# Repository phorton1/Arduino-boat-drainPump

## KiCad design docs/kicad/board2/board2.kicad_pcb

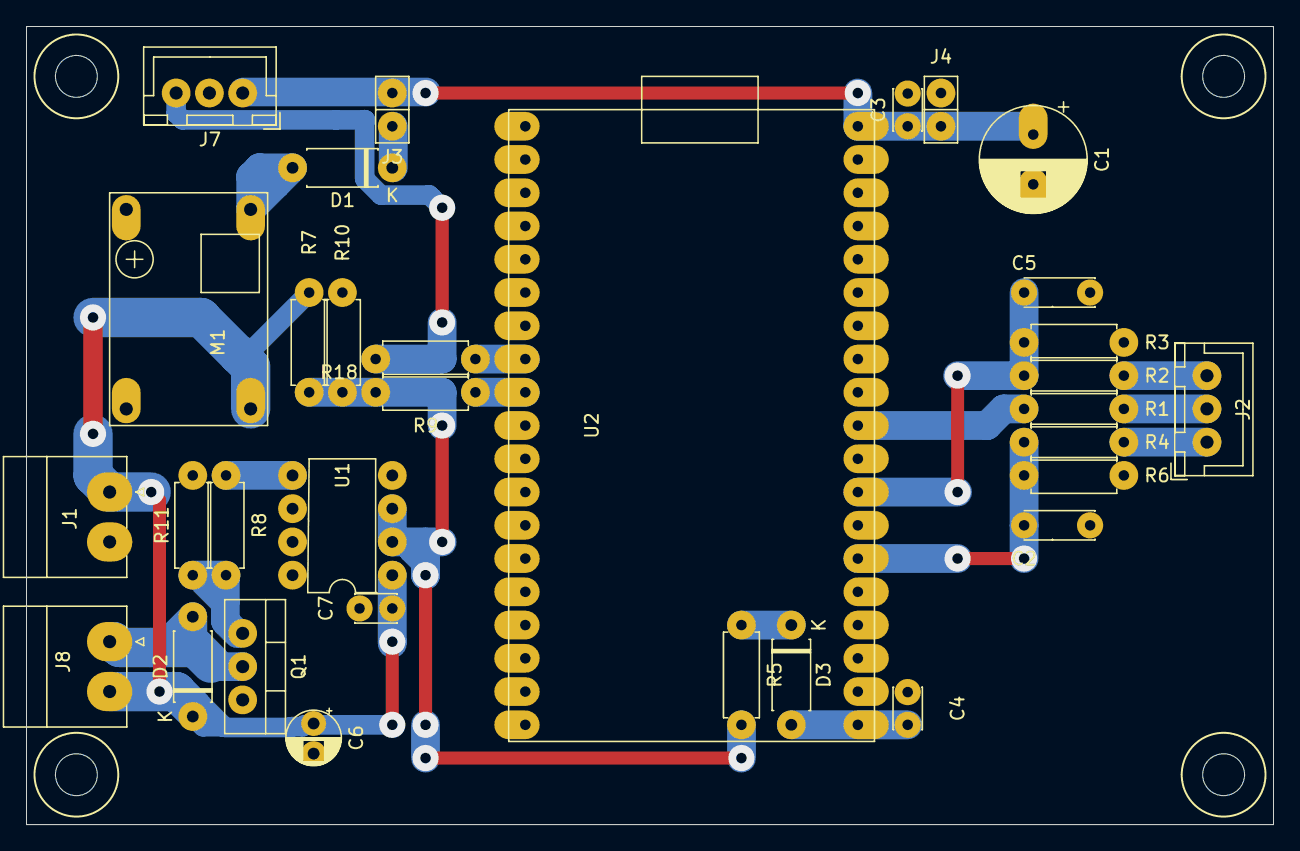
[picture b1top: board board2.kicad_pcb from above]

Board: 2 copper layers, 95.2 x 61.0 mm, 32 parts (0 on the bottom side), 20 nets.

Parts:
C1: 100uf; CP_my100uf
C2, C5: 2.2uf; myCapTantulum2
C3, C4, C7: 0.1uf; myCapCeramicSmall
C6: 10uf; CP_my10uf
D1: 1N4003; myDiodeSchotsky
D2, D3: 1N5818; myDiodeSchotsky
J1: 12 IN; myPheonix2x3.81_right
J2: SENSOR_ASSY; myJSTx03
J3: 5V Jump; myPinHeader_1x02
J4: 5V Test; myPinSocket_1x02
J7: WS2812_B; myJSTx03
J8: PUMP; myPheonix2x3.81_right
M1: BUCK01; buck-mini360
Q1: IRF520N; myThreeLegged
R1, R2, R4: 1K; myResistor
R3, R6, R7: 100K; myResistor
R5, R11: 10K; myResistor
R8: 100; myResistor
R9: 220; myResistor
R10: 33K; myResistor
R18: 330; myResistor
U1: IR2104; myDip8
U2: ESP32_DEV; esp32_dev

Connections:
+3V3: C4.1, D3.2, U2.19
+5V: C1.1, C3.1, J3.2, J4.2, J7.1, U2.1
DRIVE_ROD: J2.2, R1.1
GND: C1.2, C2.2, C3.2, C4.2, C5.2, C6.2, C7.2, J1.2, J4.1, J7.2, M1.1, M1.2, Q1.3, R3.2, R6.2, R10.2, R11.2, U1.4, U2.6, U2.20, U2.26
unnamed: D1.1, J3.1
unnamed: D1.2, M1.3
unnamed: D3.1, R5.1
unnamed: J7.3, R18.2
unnamed: Q1.1, R8.2, R11.1
unnamed: R8.1, U1.5
unnamed: R5.2, R7.2, R9.2, R10.1, U1.2, U1.3
PUMP: R9.1, U2.30
PUMP+: C6.1, C7.1, D2.1, J1.1, J8.2, M1.4, R7.1, U1.1
PUMP-: D2.2, J8.1, Q1.2
ROD_HIGH: J2.3, R2.1
ROD_LOW: J2.1, R4.1
SENSOR_HIGH: C5.1, R2.2, R3.1, U2.12
SENSOR_LOW: C2.1, R4.2, R6.1, U2.14
S_DRIVE: R1.2, U2.10
WS2812B: R18.1, U2.31

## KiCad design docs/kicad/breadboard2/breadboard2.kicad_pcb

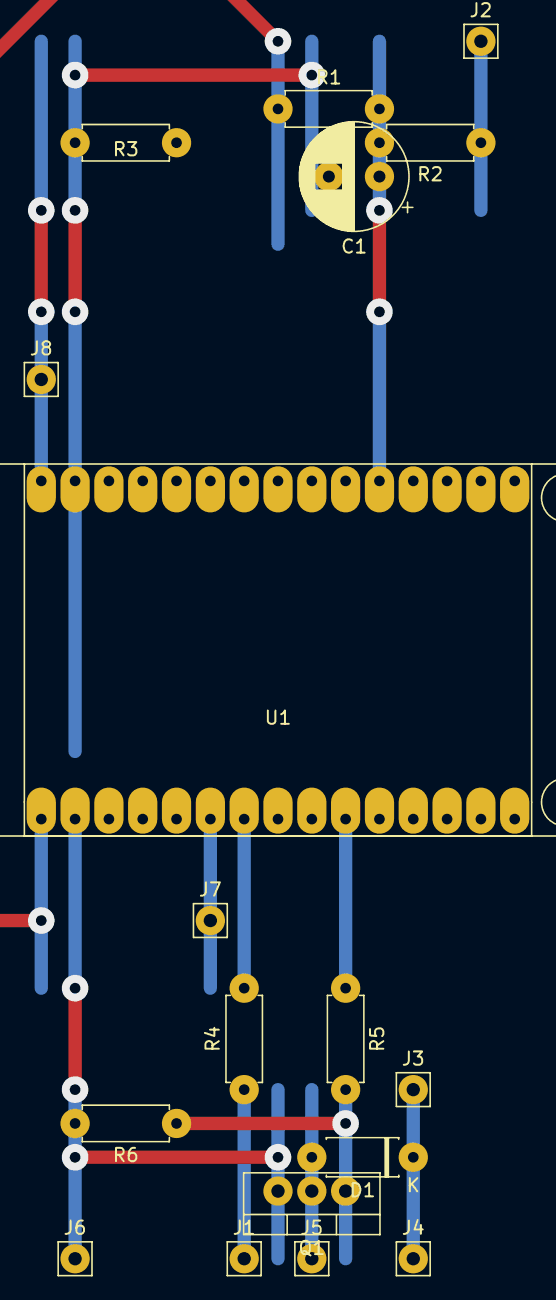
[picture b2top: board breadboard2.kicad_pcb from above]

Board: 2 copper layers, 18 parts (0 on the bottom side), 12 nets.

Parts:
C1: 1uf; CP_my100uf
D1: 1N5818; myDiodeSchotsky
J1: DRIVE_ROD; myPinHeader_1x01
J2: ROD_LOW; myPinHeader_1x01
J3: 12V; myPinHeader_1x01
J4: PUMP+; myPinHeader_1x01
J5: PUMP-; myPinHeader_1x01
J6: GND; myPinHeader_1x01
J7: WS28128B; myPinHeader_1x01
J8: 5V; myPinHeader_1x01
Q1: IRF520N; myThreeLegged
R1: 1M; myResistor
R2, R5: 220; myResistor
R3: 47K; myResistor
R4: 1K; myResistor
R6: 10K; myResistor
U1: ESP32_DEV_0; esp32_dev_0

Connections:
+3V3: R1.1, U1.30
+5V: J8.1, U1.1
DRIVE_ROD: J1.1, R4.1
GND: C1.2, J6.1, Q1.3, R3.2, R6.2, U1.2, U1.29
unnamed: Q1.1, R5.2, R6.1
PUMP: R5.1, U1.21
PUMP+: D1.1, J3.1, J4.1
PUMP-: D1.2, J5.1, Q1.2
ROD_LOW: J2.1, R2.1
SENSOR_LOW: C1.1, R1.2, R2.2, R3.1, U1.11
S_DRIVE: R4.2, U1.24
WS2812B: J7.1, U1.25

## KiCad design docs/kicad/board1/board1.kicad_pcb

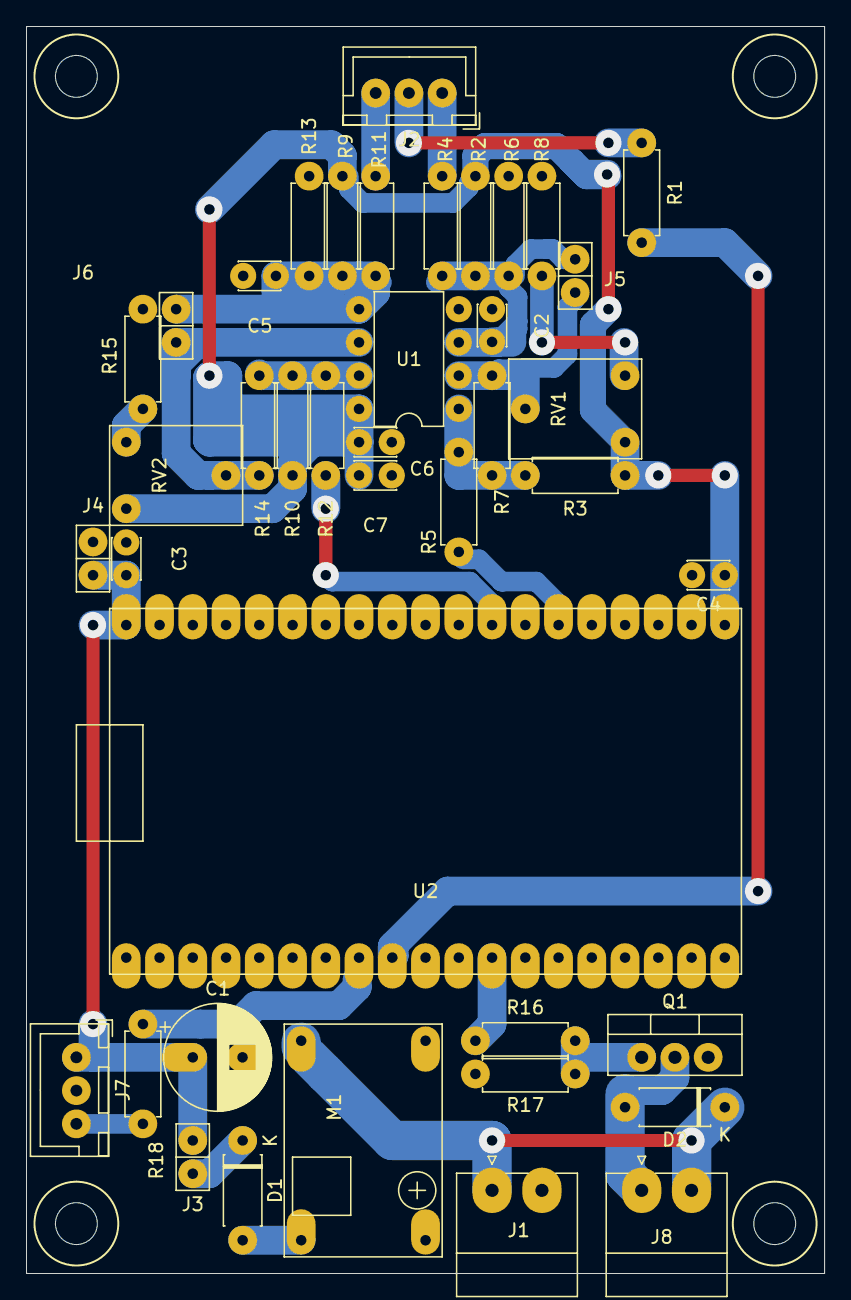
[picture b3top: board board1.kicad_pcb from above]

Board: 2 copper layers, 61.0 x 95.2 mm, 41 parts (0 on the bottom side), 25 nets.

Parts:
C1: 100uf; CP_my100uf
C2, C5, C7: 1uf; myCapCeramicSmall
C3, C4, C6: 0.1uf; myCapCeramicSmall
D1: 1N4003; myDiodeSchotsky
D2: 1N5818; myDiodeSchotsky
J1: 12 IN; myPheonix2x3.81_right
J2: SENSOR_ASSY; myJSTx03
J3: 5V Jump; myPinHeader_1x02
J4: 5V Test; myPinSocket_1x02
J5: TEST_LOW; myPinSocket_1x02
J6: TEST_HIGH; myPinSocket_1x02
J7: WS2812_B; myJSTx03
J8: PUMP; myPheonix2x3.81_right
M1: BUCK01; buck-mini360
Q1: IRF520N; myThreeLegged
R1: 1K; myResistor
R2, R9: 1M; myResistor
R3, R8, R10, R15: 4.7K; myResistor
R4, R11, R16: 220; myResistor
R5, R12: 100; myResistor
R6, R13: 47K; myResistor
R7, R14: 100K; myResistor
R17: 10K; myResistor
R18: 330; myResistor
RV1, RV2: 100K; myTrimPot
U1: LM393; DIP-8_W7.62mm
U2: ESP32_DEV; esp32_dev

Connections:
+3V3: C4.1, C6.1, C7.1, R2.1, R3.1, R9.1, R10.1, RV1.1, RV2.3, U1.8, U2.19
+5V: C1.1, C3.1, J3.2, J4.2, J7.1, U2.1
DRIVE_ROD: J2.2, R1.1
GND: C1.2, C2.2, C3.2, C4.2, C5.2, C6.2, C7.2, J1.2, J4.1, J7.2, M1.1, M1.2, Q1.3, R6.2, R8.2, R13.2, R15.2, R17.2, U1.4, U2.6, U2.20, U2.26
INPUT_HIGH: C5.1, J6.2, R9.2, R11.2, R13.1, U1.5
INPUT_LOW: C2.1, J5.2, R2.2, R4.2, R6.1, U1.3
unnamed: D1.1, J3.1
unnamed: D1.2, M1.3
unnamed: J7.3, R18.2
unnamed: Q1.1, R16.2, R17.1
unnamed: R3.2, R5.1, R7.2, U1.1
unnamed: R8.1, RV1.3
unnamed: R10.2, R12.1, R14.2, U1.7
unnamed: R15.1, RV2.1
PUMP: R16.1, U2.27
PUMP+: D2.1, J1.1, J8.2, M1.4
PUMP-: D2.2, J8.1, Q1.2
ROD_HIGH: J2.3, R11.1
ROD_LOW: J2.1, R4.1
SENSOR_HIGH: R12.2, U2.12
SENSOR_LOW: R5.2, U2.14
S_DRIVE: R1.2, U2.30
THRESH_HIGH: J6.1, R14.1, RV2.2, U1.6
THRESH_LOW: J5.1, R7.1, RV1.2, U1.2
WS2812B: R18.1, U2.31

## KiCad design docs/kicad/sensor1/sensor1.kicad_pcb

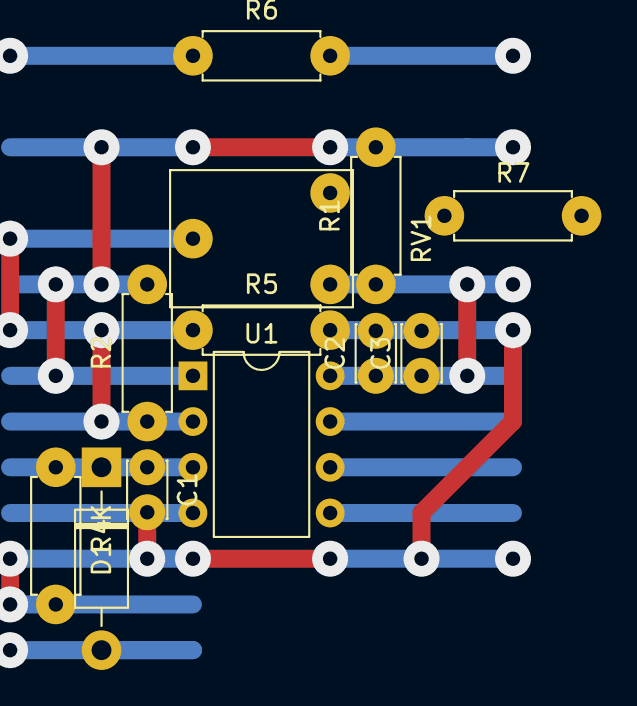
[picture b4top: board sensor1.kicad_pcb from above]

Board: 2 copper layers, 12 parts (0 on the bottom side), 6 nets.

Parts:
C1: 47nF; myCapCeramicSmall
C2: 0.1uf; myCapCeramicSmall
C3: 1uf; myCapCeramicSmall
D1: 1N5819; D_DO-41_SOD81_P10.16mm_Horizontal
R1, R7: 10k; myResistor
R2: 1M; myResistor
R4, R5: 100k; myResistor
R6: 6.8M; myResistor
RV1: 100K; myTrimPot
U1: LM393; DIP-8_W7.62mm

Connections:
+3V3: C2.1, C3.1, R1.1, RV1.1, U1.8
GND: C1.2, C2.2, C3.2, R4.2, R5.2, R7.2, U1.4
unnamed: C1.1, D1.1, R4.1, U1.3
unnamed: R1.2, R2.2, U1.1
unnamed: R2.1, R5.1, RV1.2, U1.2
unnamed: R7.1, RV1.3

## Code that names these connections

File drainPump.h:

//----------------------------------------------
// constants for drainPump.ino
//----------------------------------------------

#pragma once

#define WITH_PLOT	1

#include <myIOTDevice.h>


//=========================================================
// pins
//=========================================================
// Note that the PCB was designed using LOW=gpio34 AND
// HIGH=gpio33, but I thought there was a problem and hand
// modified the PCB to use 34/35 as shown here.
// Turns out the problem was (apparently) coupling from
// the jumper that crosses HIGH over the DRIVE signal,
// which could/should be "fixed" in future revisions of
// the board by making the pins DRIVE,HIGH,LOW, instead of
// HIGH/DRIVE/LOW.

#define PIN_PUMP		17		// inverted logic 0=on, 1=off
#define PIN_SENSOR_LOW	34
#define PIN_SENSOR_HIGH	35
#define PIN_SDRIVE		26
#define PIN_LED			16

//------------------------
// myIOT definition
//------------------------
// The pump can turn on based on two different conditions HIGH or LOW.
// The pump can turn off based on a timer or low>LOW_OFF_THRESH
// There is protection against overly long runs with MAX_TIME.
// There is added hysterisis protection with COOLDOWN_TIME

#define DRAIN_PUMP				"drain_pump"
#define DRAIN_PUMP_VERSION		"dp1.0"
#define DRAIN_PUMP_URL			"https://github.com/phorton1/Arduino-boat-drainPump"

#define DRAIN_MODE_OFF			0
#define DRAIN_MODE_FORCE		1
#define DRAIN_MODE_HIGH			2	// turns on at high>HIGH_THRESH
#define DRAIN_MODE_LOW			3	// turns on at low>LOW_THRESH
#define DRAIN_MODE_BOTH			4	// turn on at either HIGH or LOW

#define ERROR_NONE				0
#define ERROR_TOO_LONG			1	// ran for MAX_TIME seconds waiting for low to go dry
#define ERROR_ILLEGAL			2	// used to force redisplay

// CONFIGURATION

#define ID_DRAIN_MODE			"DRAIN_MODE"

#define ID_UI_INTERVAL			"UI_INTERVAL"	// int milliseconds; default=1000; min=1000; max=30000 (5 minutes)
	// How often do we update the webUI.

#define ID_CHK_INTERVAL			"CHK_INTERVAL"	// int milliseconds; Default=5000; min=100; max=30000 (30 seconds)
	// How often do we sample the sensors into the circular buffers when the pump is off
	// We sense once per second once the pump is on.

#define ID_NUM_SAMPLES			"NUM_SAMPLES"	// int; default=5, min=1, max=60;
	// The number of samples in the circular buffer.
	// This is coupled with CHK_INTERVAL to determine the actual update frequency for turning the pump ON,
	// and the one second fixed interval for turning the pump off

#define ID_HIGH_THRESH			"HIGH_THRESH"		// int; default=20;   min=1; max=4094;
#define ID_LOW_THRESH			"LOW_THRESH"		// int; default=500;  min=1; max=4094;
#define ID_LOW_OFF_THRESH		"LOW_OFF_THRESH"	// int; default=50;	  min=10; max=4094;
	// Thresholds for turning the pump on and off.
	// LOW_OFF_THRESH must be substantially below LOW_THRESH

#define ID_RUN_TIME				"RUN_TIME"				// int seconds; Default=0; min=0; max=180 (3 minutes)
	// If non-zero this will put the pump in "timer" mode where it will turn off after running for
	// this many seconds; If zero the pump will turn off based on LOW_OFF_THRESH.
	// Must be less than MAX_TIME if non-zero

#define ID_MAX_TIME				"MAX_TIME"			// int seconds; Default=120; min=30; Max=360	(6 minutes)
	// In any automatic mode the pump will be turned off after this many seconds in case the LOW (SENSOR_LOW).
	// never indicates dry.

#define ID_COOLDOWN_TIME		"COOLDOWN_TIME"		// int seconds; Default=30 seconds; Min=10; Max=900 (15 minutes)
	// After a HIGH/BOTH pump run, we will wait this many seconds before begining
	// another HIGH/BOTH pump run.  The counter is cleared when the DRAIN_MODE is changed


// USER INTERFACE

#define ID_CLEAR_ERROR			"CLEAR_ERROR"		// a UI command to clear the error state, if any
#define ID_LED_BRIGHTNESS		"LED_BRIGHTNESS"	// int; Default=32; min=10; max=255
#define ID_HISTORY_LINK     	"HISTORY"
#define ID_CHART_LINK			"CHART"


// STATE

#define ID_STATE_STRING			"STATE_STRING"		// readonly string formatted according to the state upon changes
#define ID_ERROR_CODE			"ERROR_CODE"		// enum; default "", "TOO_LONG"	cleared with clearError() UI command

#define ID_TIME_LAST_RUN    	"TIME_LAST_RUN"		// statistics regarding the last completed run
#define ID_DUR_LAST_RUN     	"DUR_LAST_RUN"
#define ID_SINCE_LAST_RUN   	"SINCE_LAST_RUN"




class drainPump : public myIOTDevice
{
public:

    drainPump() {}
    ~drainPump() {}

	static uint32_t _drain_mode;		// enum
	static int		_ui_interval;		// milliseconds
	static int		_chk_interval;		// milliseconds
	static int		_num_samples;		// int
	static int		_high_thresh;		// vs average of analog reads
	static int		_low_thresh;		// vs average of analog reads
	static int		_low_off_thresh;	// vs average of analog reads
	static int		_run_time;			// seconds
	static int		_max_time;			// seconds
	static int		_cooldown_time;		// seconds

	static String 	_state_string;		// built string
 	static uint32_t	_error_code;		// enum
	static int		_led_brightness;	// 1..254
	static String 	_history_link;		// built string
	static String 	_chart_link;		// built string

    static time_t   _time_last_run;
    static int      _since_last_run;
    static int      _dur_last_run;

	static void onDrainModeChanged(const myIOTValue *value, uint32_t val);
	static void onRunTimeChanged(const myIOTValue *value, int val);
	static void onBrightnessChanged(const myIOTValue *desc, uint32_t val);
	static void clearError();
    virtual String onCustomLink(const String &path,  const char **mime_type) override;

	void updateUI();
	void handlePump();
	void handlePixels();
	void endRun(time_t time_now);
	int readSensor(int pin, int *avg);
	static void pumpOn(bool on);

	// public state variables to drainHistory.pm

	static time_t m_run_start;
	static uint32_t m_error_code;

	// plotting

	#if WITH_PLOT
		virtual bool hasPlot() override    { return true; }
	#endif

};






extern enumValue errorCodes[];

extern drainPump *drain_pump;

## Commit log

2025-11-30 initial commit (after prototyping sensor board)
2025-11-30 added LICENSE.TXT
2025-12-01 checkin PCB design and new schematic before building
2025-12-03 finish drainPump PCB and myIOT implementation
2025-12-05 changed FACTORY_RESET defaults; added "FORCE" message to drainHistory report
2025-12-05 checking uilt fusiion and prusa 3DP files
2025-12-07 Rework circuit design entirely to analogRead() doing away with LM393 and discovering rich signal hiding beneath it. Unfortunately I don't have an digital signal mosfets on hand so I reworked the pump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
2025-12-11 complete drainPump pcb board2
2025-12-15 submodule(data) auto_commit(b649fc3a) iotChart.js - added scheme for setting device specific series colors
2025-12-16 Implemented incremental chart updating in iotChart.js and removed drain_pump widget iotChart.js *should* be upward compatible with everything except the bilgeAlarm "error" widget. Henceforth NO MORE 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
2025-12-16 update drain pump data submodule
2025-12-17 added LOW_ON mode; pump can come on HIGH_ON or LOW_ON, off by LOW_OFF_THRESH or TIMED mode, which is now driven by RUN_TIME param;
2025-12-18 reworked iotChart.js incremental update scheme starting with Arduino-boat-drainPump
2025-12-18 submodule(data) auto_commit(1adaeb45) reworked iotChart.js incremental update scheme starting with Arduino-boat-drainPump
2025-12-18 submodule(data) auto_commit(b6ac0c88) starting in Arduino-boat-arirco, major rework of iotChart.js and how charts are implemented - use common chart.html instead of specific/extra_data/device_chart.h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
2025-12-18 bring drain_pump up to new iotChart implementation
2025-12-18 commit parent manually
2025-12-18 submodule(data) auto_commit(78894e93) change onChartResize() to use create_chart() instead of built in jqplot.replot()
2025-12-18 submodule(data) auto_commit(40916b0c) separate iotChart.js doChart() as init only method from onXXX() UI methods - yet another rework of iotChart.js and myIOTDataLog starting with fridgeController
2025-12-18 submodule(data) auto_commit(b923e44d) back to static html for chart.html; got rid of myIOTDataLog::getChartHtml() starting with tempController
2025-12-18 bring up to latest data/iotChart.js and data/chart.html
2025-12-18 submodule(data) auto_commit(a4e2ed81) change chart.html and iotChart.js to use and remove style "degree_hidden" for devices that chart things with degrees
2025-12-18 submodule(data) auto_commit(a9754dbc) fixed renamed control _degree_type
2025-12-18 submodule(data) auto_commit(03555741) fix malformed chart.html <select id='_chart_period'> text
2025-12-19 re-implement upward only drainHistory when the pump is off
2025-12-19 submodule(data) auto_commit(1cb3d61a) add onChartResize() back to chart.html
2025-12-19 submodule(data) auto_commit(253976a9) more changes to iotChart.js starting with tempController so at least refresh works *well* if no zooming involved
2025-12-19 commit parents
2025-12-20 submodule(data) auto_commit(eccd1fcc) iotChart.js - added save/restore of series visibility and refactored code
2025-12-30 Added "BOTH" mode and charting of downward moves, even when pump is off, of >50 in sensor values
2025-12-31 submodule(data) auto_commit(2a8db875) add degree_type to myIOT chart_header for use in initializing iotChart.js
